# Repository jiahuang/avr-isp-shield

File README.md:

#Arduino AVR Programming Shield

Use an Arduino Uno to program other AVR chips by hooking up MOSI, MISO, SCK, RST, VCC, and GND for you so your fat fingers don't mess up the programming circuit while trying to pull out the programmed chip. 

Designed for the following, but will work with chips that have the same pin setup:
* ATMega328/ATMega168 (28 pin)
* ATTiny 24/44/84 (14 pin)
* ATTiny 25/45/85 (8 pin)

Things that it does (differently?) from other AVR programming shields:
* Has a protoboard
* Breaks out all the pins for programmed chips. In case you actually programmed the chip to do something. 
* Breaks out XTAL1 & 2 pins for programming with an external crystal ocsillator
* LED indicators on heartbeat/error/programming. The LEDs even include resistors so you won't get blinded watching for error signals.
* Reset button for resetting the programmed chip without a power cycle
* Slide switch to turn on/off the 10uF connecting cap between reset and ground. Because putting in and taking out a cap is too difficult.

##The finished board
![Finished board](https://raw.github.com/jiahuang/avr-isp-shield/master/images/shield_final.jpg
)

##The board
![The board](https://raw.github.com/jiahuang/avr-isp-shield/master/images/board.png
)

##References
* [Sparkfun eagle libraries](https://github.com/sparkfun/SparkFun-Eagle-Libraries)
* [MIT HighLowTech](http://hlt.media.mit.edu/?p=1695)
* [Arduino AVR MegaISP](http://playground.arduino.cc/Code/MegaISP)

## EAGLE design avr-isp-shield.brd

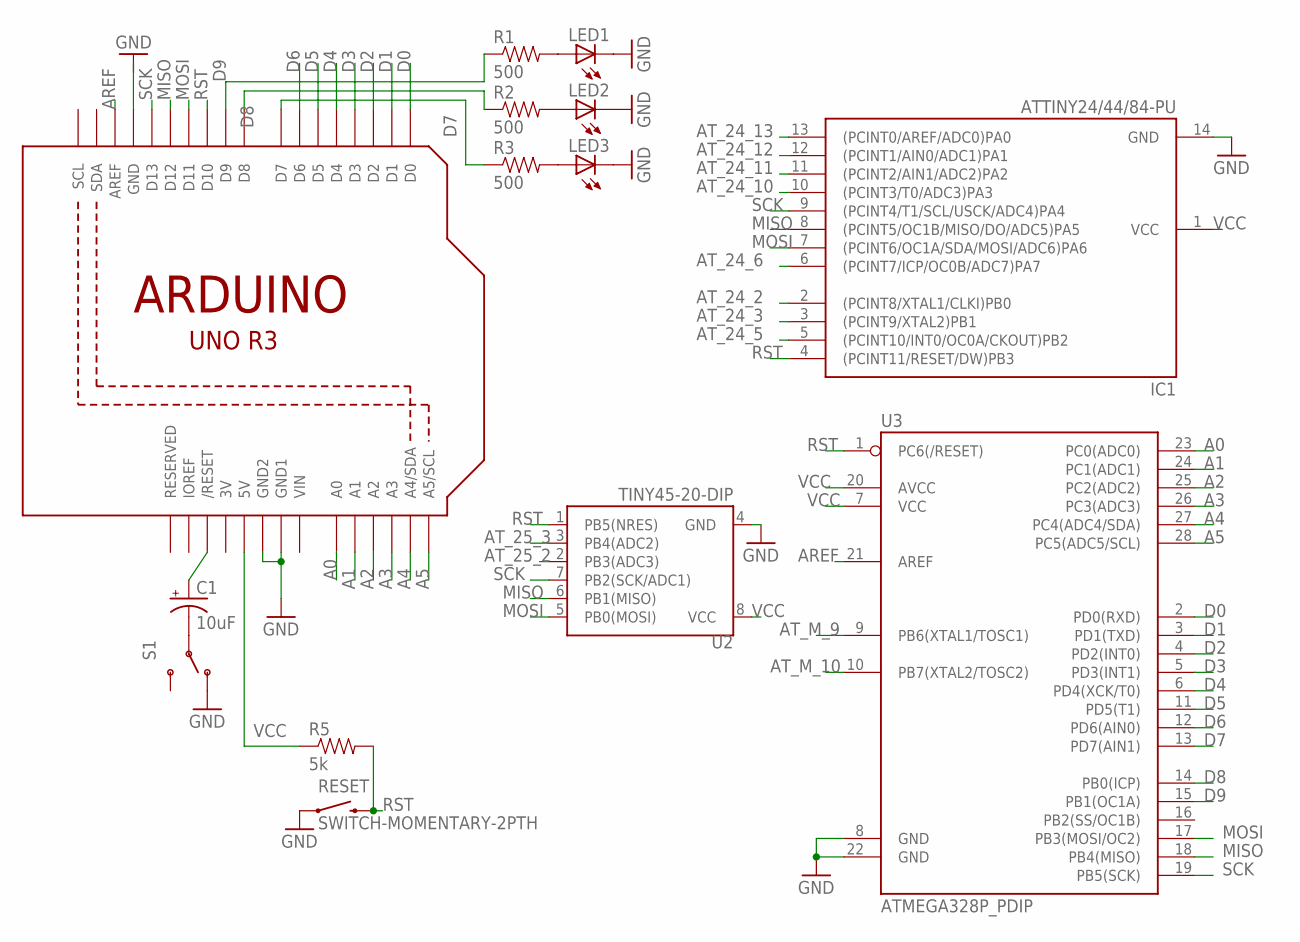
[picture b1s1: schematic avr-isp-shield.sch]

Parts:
C1: 10uF; CPOL-RADIAL-10UF-25V
IC1: ATTINY24/44/84-PU; DIL14
LED1, LED2, LED3: LED3MM
R1, R2, R3: 500; AXIAL-0.3
R5: 5k; AXIAL-0.3
RESET: SWITCH-MOMENTARY-2PTH; TACTILE-PTH
S1: SWITCH-SPDTPTH; SWITCH-SPDT
U2: TINY45-20-DIP; DIP08
U3: ATMEGA328P_PDIP; DIL28-3
U4: ARDUINOR3-DIMENSION; ARDUINOR3

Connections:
3V: U4.3V
A0: U3.23 (PC0(ADC0)), U4.A0
A1: U3.24 (PC1(ADC1)), U4.A1
A2: U3.25 (PC2(ADC2)), U4.A2
A3: U3.26 (PC3(ADC3)), U4.A3
A4: U3.27 (PC4(ADC4/SDA)), U4.A4 (A4/SDA)
A5: U3.28 (PC5(ADC5/SCL)), U4.A5 (A5/SCL)
AREF: U3.21 (AREF), U4.AREF
AT_24_2: IC1.2 ((PCINT8/XTAL1/CLKI)PB0)
AT_24_3: IC1.3 ((PCINT9/XTAL2)PB1)
AT_24_5: IC1.5 ((PCINT10/INT0/OC0A/CKOUT)PB2)
AT_24_6: IC1.6 ((PCINT7/ICP/OC0B/ADC7)PA7)
AT_24_10: IC1.10 ((PCINT3/T0/ADC3)PA3)
AT_24_11: IC1.11 ((PCINT2/AIN1/ADC2)PA2)
AT_24_12: IC1.12 ((PCINT1/AIN0/ADC1)PA1)
AT_24_13: IC1.13 ((PCINT0/AREF/ADC0)PA0)
AT_25_2: U2.2 (PB3(ADC3))
AT_25_3: U2.3 (PB4(ADC2))
AT_M_9: U3.9 (PB6(XTAL1/TOSC1))
AT_M_10: U3.10 (PB7(XTAL2/TOSC2))
D0: U3.2 (PD0(RXD)), U4.D0
D1: U3.3 (PD1(TXD)), U4.D1
D2: U3.4 (PD2(INT0)), U4.D2
D3: U3.5 (PD3(INT1)), U4.D3
D4: U3.6 (PD4(XCK/T0)), U4.D4
D5: U3.11 (PD5(T1)), U4.D5
D6: U3.12 (PD6(AIN0)), U4.D6
D7: R3.P$1 (1), U3.13 (PD7(AIN1)), U4.D7
D8: R2.P$1 (1), U3.14 (PB0(ICP)), U4.D8
D9: R1.P$1 (1), U3.15 (PB1(OC1A)), U4.D9
GND: IC1.14 (GND), LED1.K (C), LED2.K (C), LED3.K (C), RESET.1, S1.1 (O), U2.4 (GND), U3.8 (GND), U3.22 (GND), U4.GND1, U4.GND2
MISO: IC1.8 ((PCINT5/OC1B/MISO/DO/ADC5)PA5), U2.6 (PB1(MISO)), U3.18 (PB4(MISO)), U4.D12
MOSI: IC1.7 ((PCINT6/OC1A/SDA/MOSI/ADC6)PA6), U2.5 (PB0(MOSI)), U3.17 (PB3(MOSI/OC2)), U4.D11
unnamed: C1.1 (+), U4.RESET (/RESET)
unnamed: C1.2 (-), S1.2
unnamed: LED1.A, R1.P$2 (2)
unnamed: LED2.A, R2.P$2 (2)
unnamed: LED3.A, R3.P$2 (2)
RST: IC1.4 ((PCINT11/RESET/DW)PB3), R5.P$2 (2), RESET.3 (2), U2.1 (PB5(NRES)), U3.1 (PC6(/RESET)), U4.D10
SCK: IC1.9 ((PCINT4/T1/SCL/USCK/ADC4)PA4), U2.7 (PB2(SCK/ADC1)), U3.19 (PB5(SCK)), U4.D13
VCC: IC1.1 (VCC), R5.P$1 (1), U2.8 (VCC), U3.7 (VCC), U3.20 (AVCC), U4.5V
VIN: U4.VIN

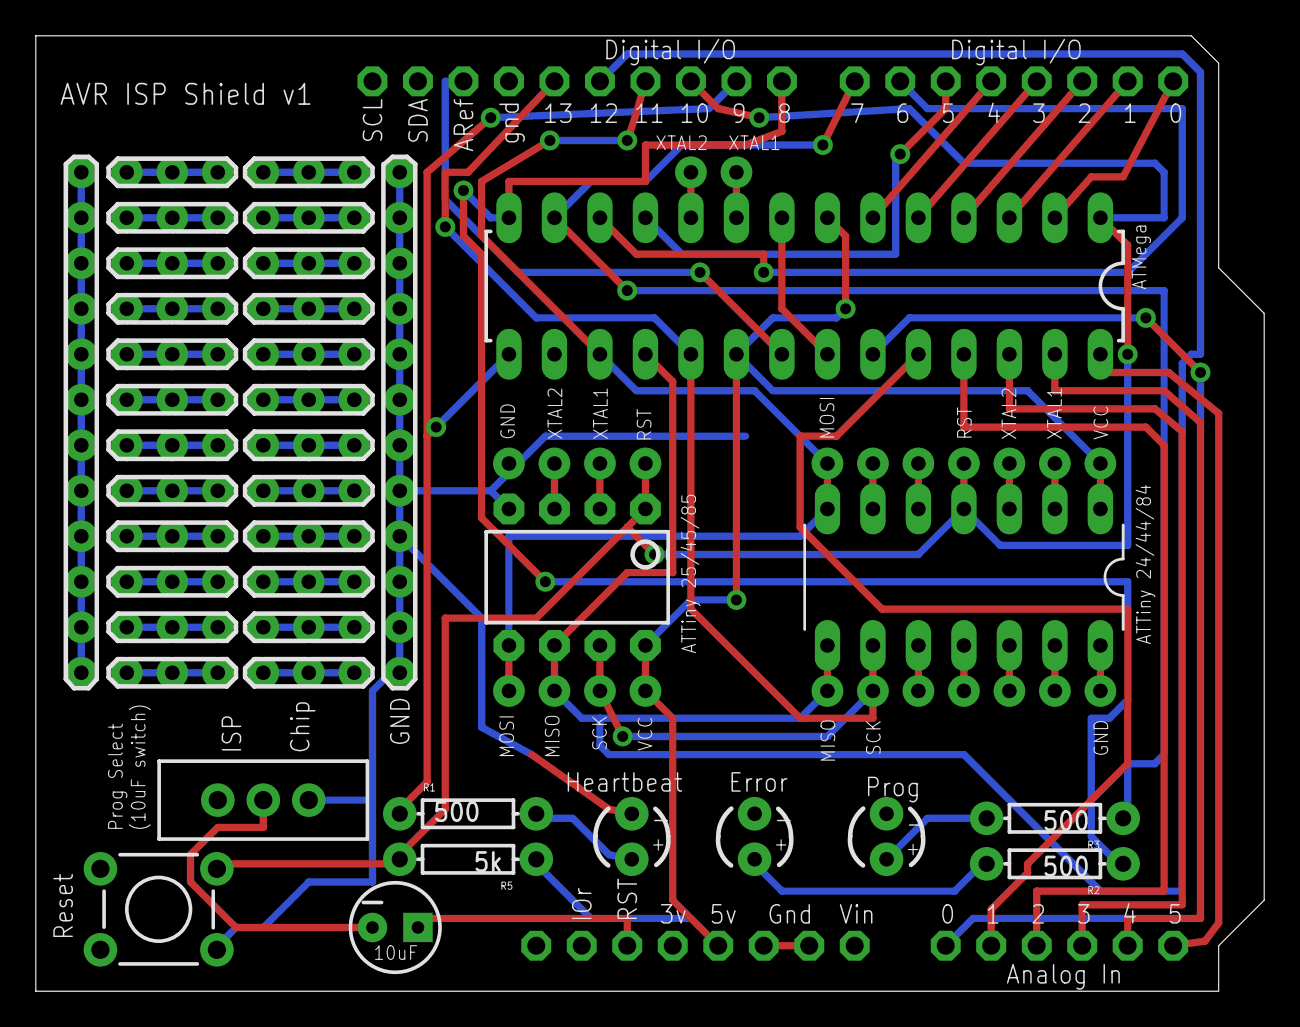
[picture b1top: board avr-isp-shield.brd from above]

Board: 2 copper layers, 68.6 x 53.3 mm, 14 parts (0 on the bottom side), 28 nets.

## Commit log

2012-12-28 initial eagle project
2012-12-28 images of the board
2012-12-28 adding readme
2012-12-28 adding ignore file
2012-12-28 updating readme
2012-12-28 adding a name
2012-12-29 added ground pours
2012-12-29 routing SCK correctly
2012-12-30 updating board
2013-02-06 added final image

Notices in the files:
parts and their libraries:
SparkFun-DigitalIC: Licensing: CC v3.0 Share-Alike You are welcome to use this library for commercial purposes.
